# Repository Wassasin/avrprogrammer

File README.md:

# avrprogrammer
ATtiny13 programmer PCB in EagleCAD

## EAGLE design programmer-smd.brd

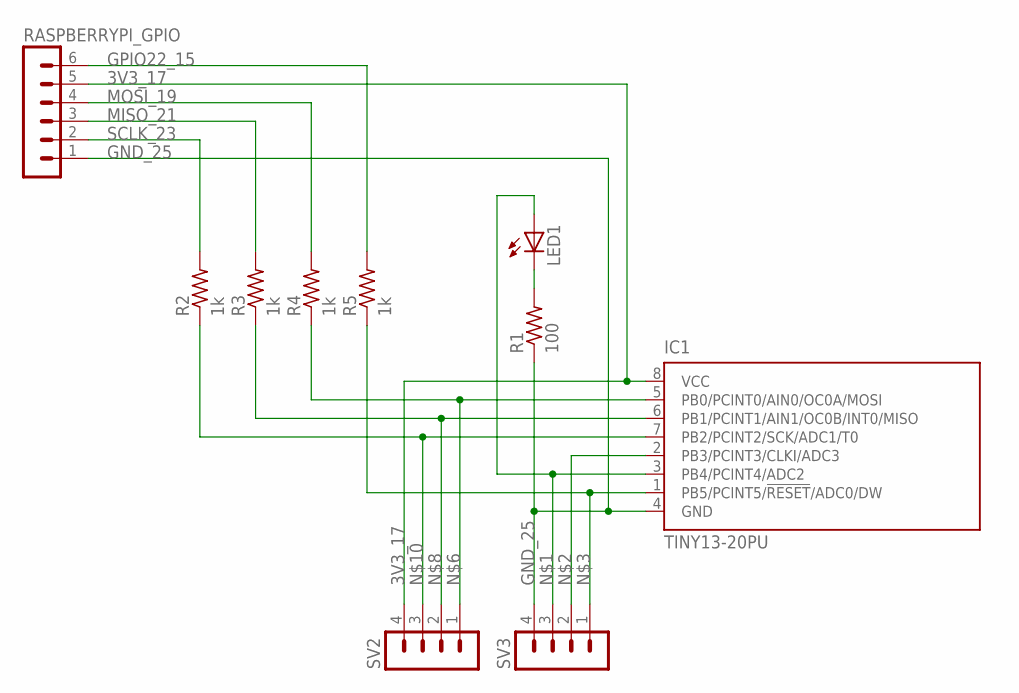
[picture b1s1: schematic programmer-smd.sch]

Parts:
IC1: TINY13-20PU; DIL08
LED1: LEDCHIP-LED0805; CHIP-LED0805
R1: 100; M0805
R2, R3, R4, R5: 1k; M0805
RASPBERRYPI_GPIO: MA06-1
SV2, SV3: MA04-1

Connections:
3V3_17: IC1.8 (VCC), RASPBERRYPI_GPIO.5, SV2.4
GND_25: IC1.4 (GND), R1.1, RASPBERRYPI_GPIO.1, SV3.4
GPIO22_15: R5.2, RASPBERRYPI_GPIO.6
MISO_21: R3.2, RASPBERRYPI_GPIO.3
MOSI_19: R4.2, RASPBERRYPI_GPIO.4
unnamed: IC1.3 (PB4/PCINT4/ADC2), LED1.A, SV3.3
unnamed: IC1.2 (PB3/PCINT3/CLKI/ADC3), SV3.2
unnamed: IC1.1 (PB5/PCINT5/!RESET!/ADC0/DW), R5.1, SV3.1
unnamed: LED1.C, R1.2
unnamed: IC1.5 (PB0/PCINT0/AIN0/OC0A/MOSI), R4.1, SV2.1
unnamed: IC1.6 (PB1/PCINT1/AIN1/OC0B/INT0/MISO), R3.1, SV2.2
unnamed: IC1.7 (PB2/PCINT2/SCK/ADC1/T0), R2.1, SV2.3
SCLK_23: R2.2, RASPBERRYPI_GPIO.2

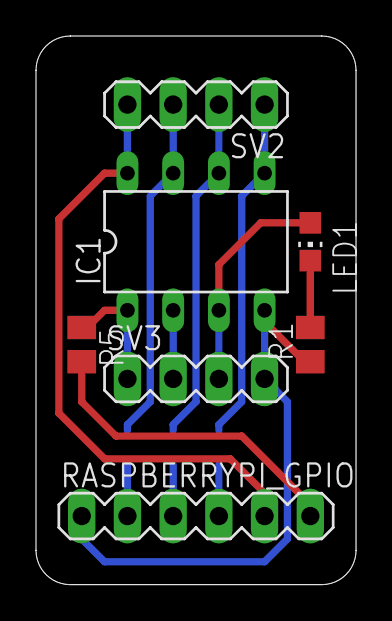
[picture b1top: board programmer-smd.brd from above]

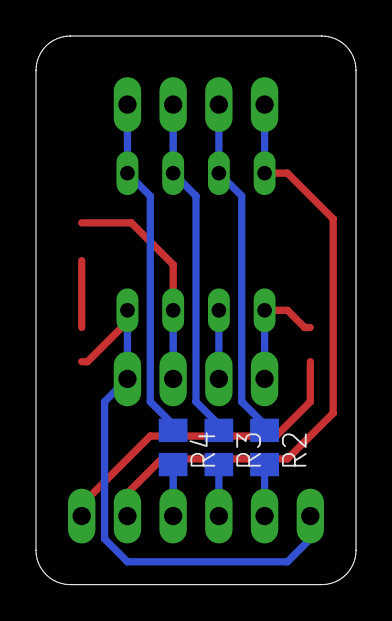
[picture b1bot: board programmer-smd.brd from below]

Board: 2 copper layers, 17.8 x 30.5 mm, 10 parts (3 on the bottom side), 13 nets.

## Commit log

2016-05-03 Added copyright
2016-05-03 Added resistor values
2016-05-03 Last text revisions
2016-05-10 Added image
